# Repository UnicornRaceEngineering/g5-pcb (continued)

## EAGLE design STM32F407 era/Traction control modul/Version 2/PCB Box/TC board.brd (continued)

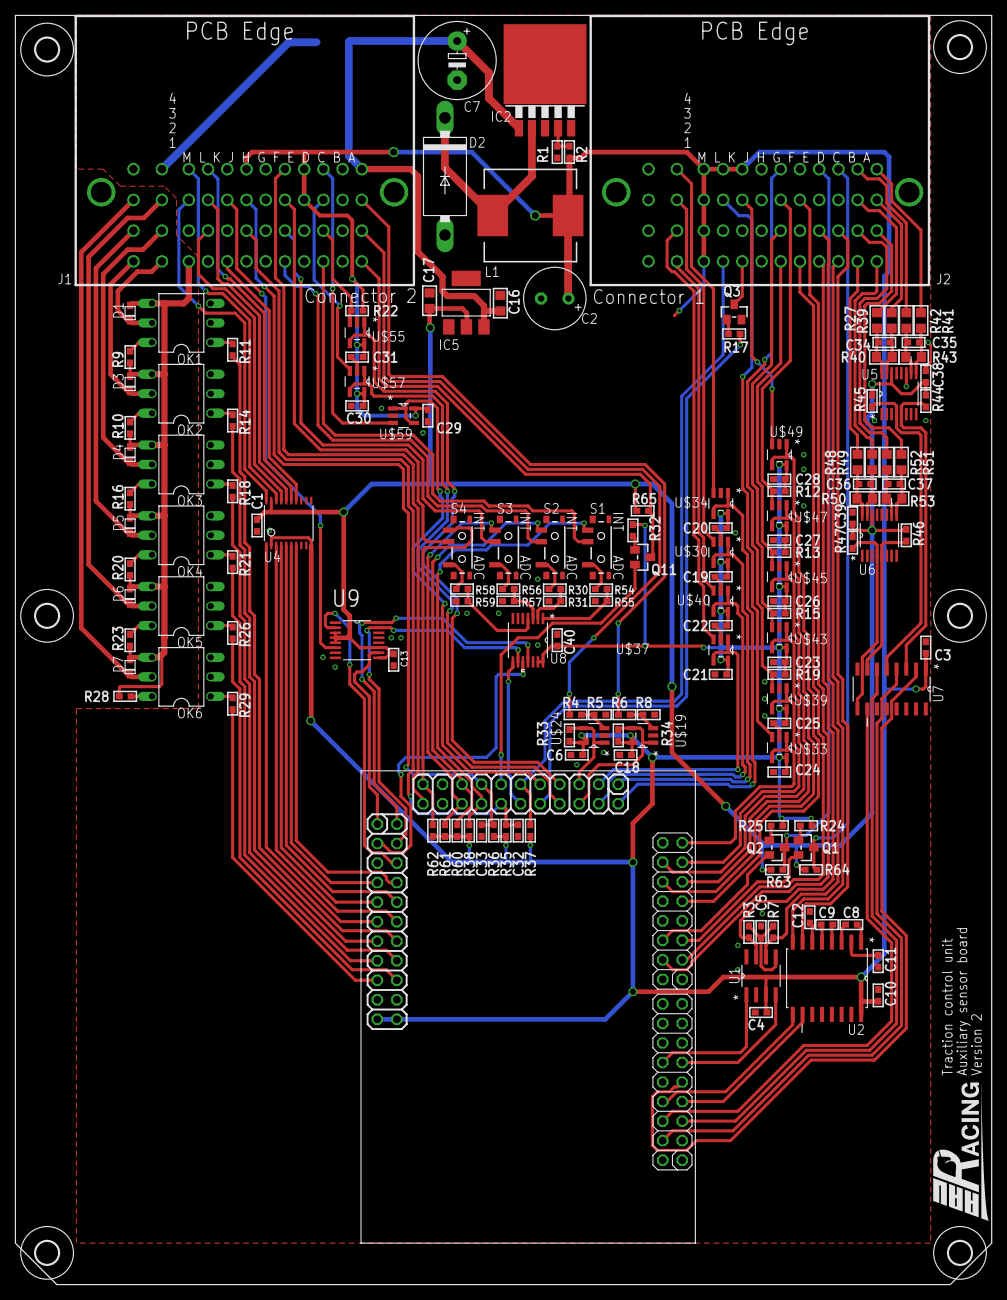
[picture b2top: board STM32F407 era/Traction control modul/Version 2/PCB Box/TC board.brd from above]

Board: 2 copper layers, 127.0 x 165.1 mm, 160 parts (1 on the bottom side), 156 nets.

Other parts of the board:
U9: AD5024BRUZ; SOP65P640X120-16N

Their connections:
5.0V: U9.3, U9.4, U9.5, U9.9, U9.11; also elsewhere on the board
DACCLR: U9.10; also elsewhere on the board
DACCS: U9.2; also elsewhere on the board
GND: U9.8, U9.14; also elsewhere on the board
MOSI: U9.15; also elsewhere on the board
SCK: U9.16; also elsewhere on the board
VOUT: U9.6; also elsewhere on the board

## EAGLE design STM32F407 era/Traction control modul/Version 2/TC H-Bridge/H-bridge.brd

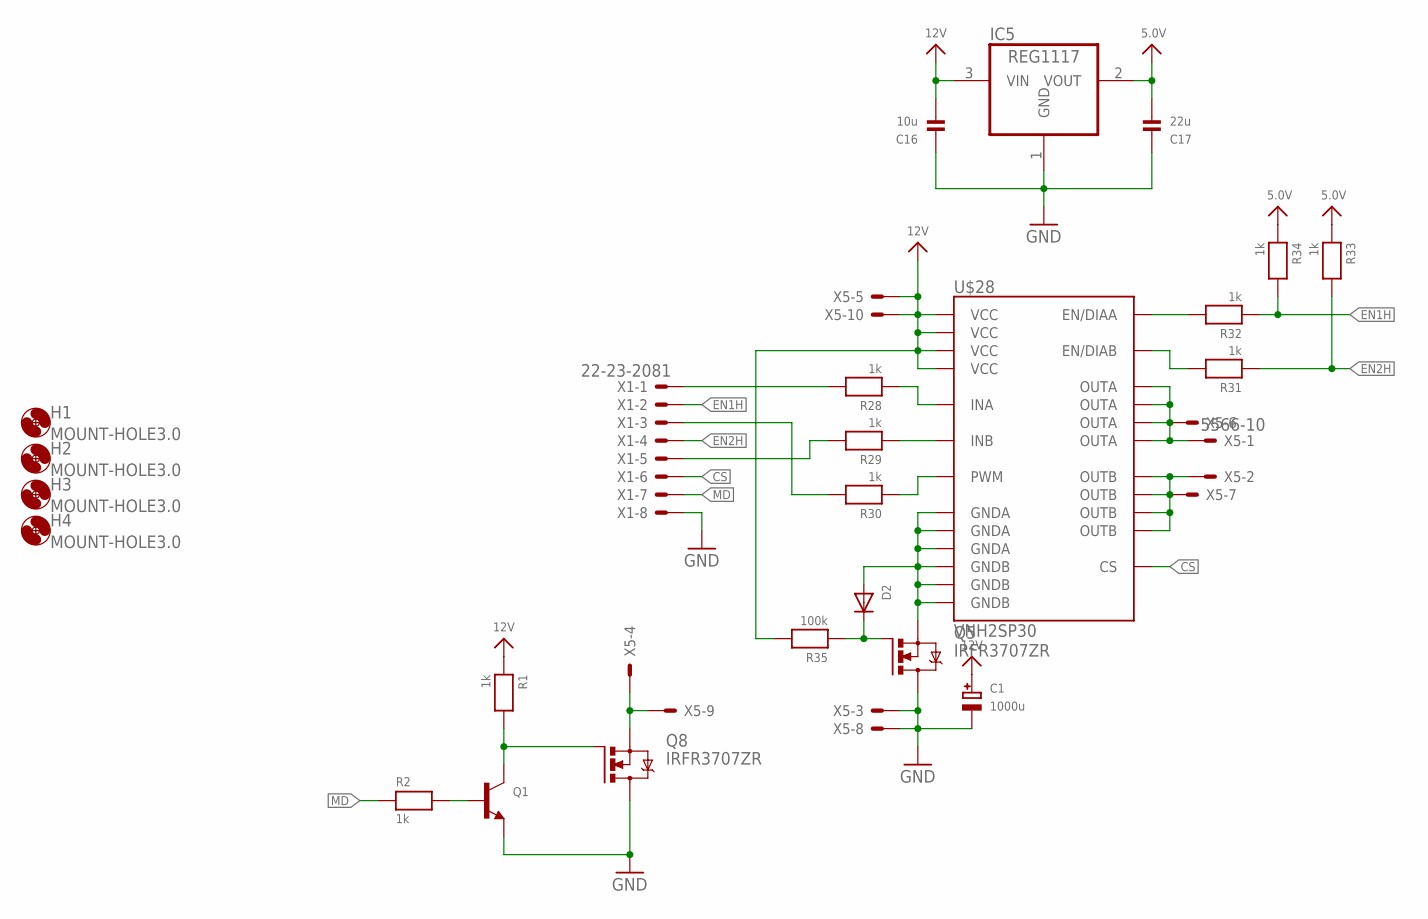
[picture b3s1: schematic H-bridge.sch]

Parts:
C1: 1000u; CELEC_3.5MM_10MM
C16: 10u; _0805
C17: 22u; _0805
D2: DIODESMA; SMADIODE
H1, H2, H3, H4: MOUNT-HOLE3.0; 3,0
IC5: REG1117; SOT223
Q1: TRANSISTOR_NPNWIDE; SOT23-WIDE
Q5, Q8: IRFR3707ZR; D-PAK_TO252AA
R1, R2, R28, R29, R30, R31, R32, R33, R34: 1k; _0603
R35: 100k; _0603
U$28: VNH2SP30
X1: 22-23-2081
X5: 5566-10

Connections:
5.0V: C17.2, IC5.2 (VOUT), R33.1, R34.1
12V: C1.+, C16.2, IC5.3 (VIN), R1.1, R35.2, U$28.3 (VCC), U$28.13 (VCC), U$28.23 (VCC), U$28.SLUG1 (VCC), X5.5, X5.10
CS: U$28.9 (CS), X1.6
CVVM: U$28.15 (OUTB), U$28.16 (OUTB), U$28.21 (OUTB), U$28.SLUG2 (OUTB), X5.2, X5.7
EN1H: R32.1, R34.2, X1.2
EN2H: R31.1, R33.2, X1.4
GND: C1.-, C16.1, C17.1, IC5.1 (GND), Q1.2 (E), Q5.4 (D), Q8.4 (D), X1.8, X5.3, X5.8
GNDM: Q8.3 (S), X5.4, X5.9
GNDS: D2.A, Q5.3 (S), U$28.18 (GNDB), U$28.19 (GNDB), U$28.20 (GNDB), U$28.26 (GNDA), U$28.27 (GNDA), U$28.28 (GNDA)
MD: R2.1, X1.7
unnamed: Q1.1 (B), R2.2
unnamed: Q1.3 (C), Q8.1 (G), R1.2
unnamed: R30.1, U$28.8 (PWM)
unnamed: R29.1, U$28.11 (INB)
unnamed: R28.1, U$28.5 (INA)
unnamed: R31.2, U$28.10 (EN/DIAB)
unnamed: R32.2, U$28.6 (EN/DIAA)
unnamed: D2.C, Q5.1 (G), R35.1
unnamed: R28.2, X1.1
unnamed: R29.2, X1.5
unnamed: R30.2, X1.3
OUTA: U$28.1 (OUTA), U$28.25 (OUTA), U$28.30 (OUTA), U$28.SLUG3 (OUTA), X5.1, X5.6

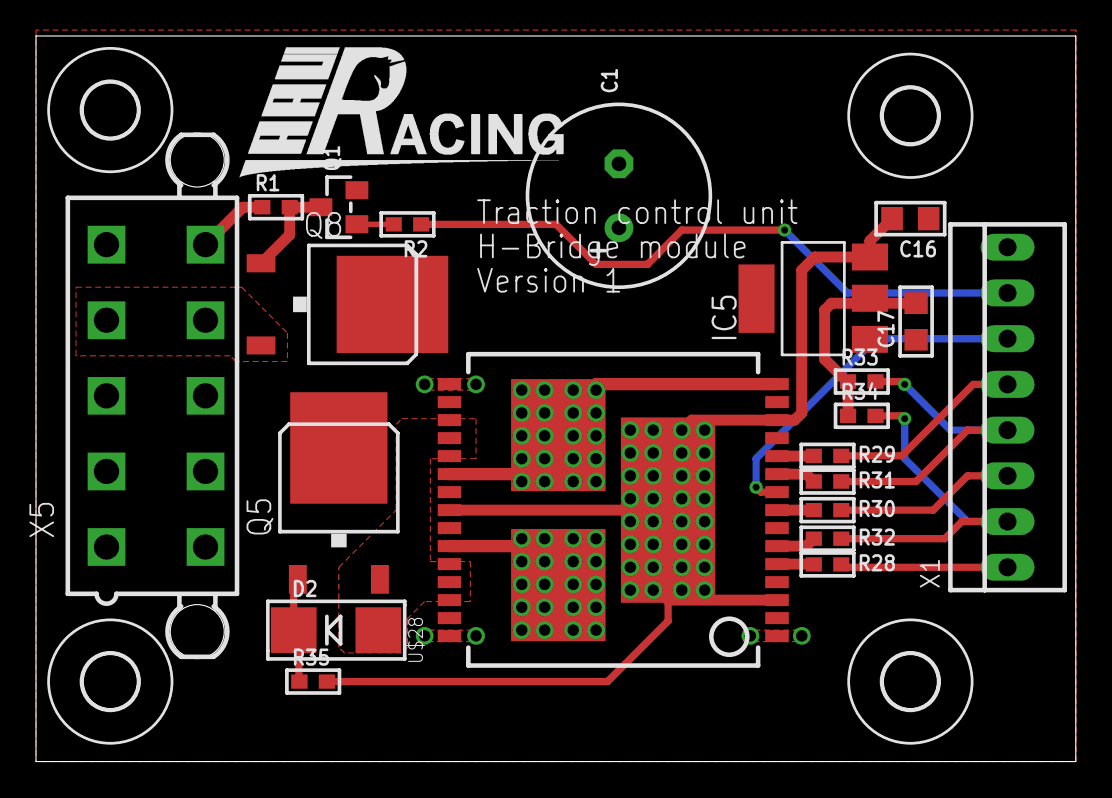
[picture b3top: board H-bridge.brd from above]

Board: 2 copper layers, 57.8 x 40.3 mm, 25 parts (0 on the bottom side), 22 nets.

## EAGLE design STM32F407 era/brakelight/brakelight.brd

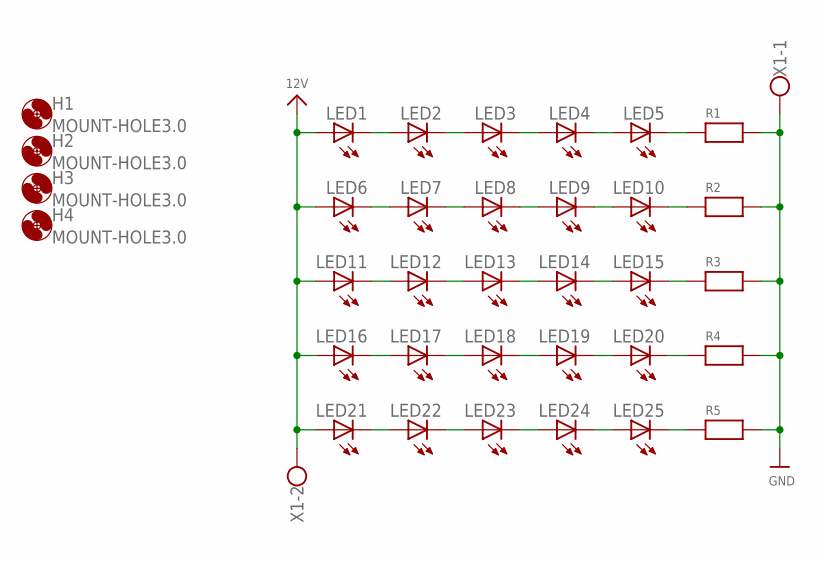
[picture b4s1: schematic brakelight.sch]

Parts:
H1, H2, H3, H4: MOUNT-HOLE3.0; 3,0
LED1, LED2, LED3, LED4, LED5, LED6, LED7, LED8, LED9, LED10, LED11, LED12, LED13, LED14, LED15, LED16, LED17, LED18, LED19, LED20, LED21, LED22, LED23, LED24, LED25: LEDP-LCC-2; P-LCC-2
R1, R2, R3, R4, R5: RESISTOR0805; 0805
X1: W237-102

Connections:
12V: LED1.A, LED6.A, LED11.A, LED16.A, LED21.A, X1.2
GND: R1.2, R2.2, R3.2, R4.2, R5.2, X1.1
unnamed: LED1.C, LED2.A
unnamed: LED6.C, LED7.A
unnamed: LED11.C, LED12.A
unnamed: LED16.C, LED17.A
unnamed: LED21.C, LED22.A
unnamed: LED2.C, LED3.A
unnamed: LED7.C, LED8.A
unnamed: LED12.C, LED13.A
unnamed: LED17.C, LED18.A
unnamed: LED22.C, LED23.A
unnamed: LED3.C, LED4.A
unnamed: LED8.C, LED9.A
unnamed: LED13.C, LED14.A
unnamed: LED18.C, LED19.A
unnamed: LED23.C, LED24.A
unnamed: LED4.C, LED5.A
unnamed: LED9.C, LED10.A
unnamed: LED14.C, LED15.A
unnamed: LED19.C, LED20.A
unnamed: LED24.C, LED25.A
unnamed: LED5.C, R1.1
unnamed: LED10.C, R2.1
unnamed: LED15.C, R3.1
unnamed: LED20.C, R4.1
unnamed: LED25.C, R5.1

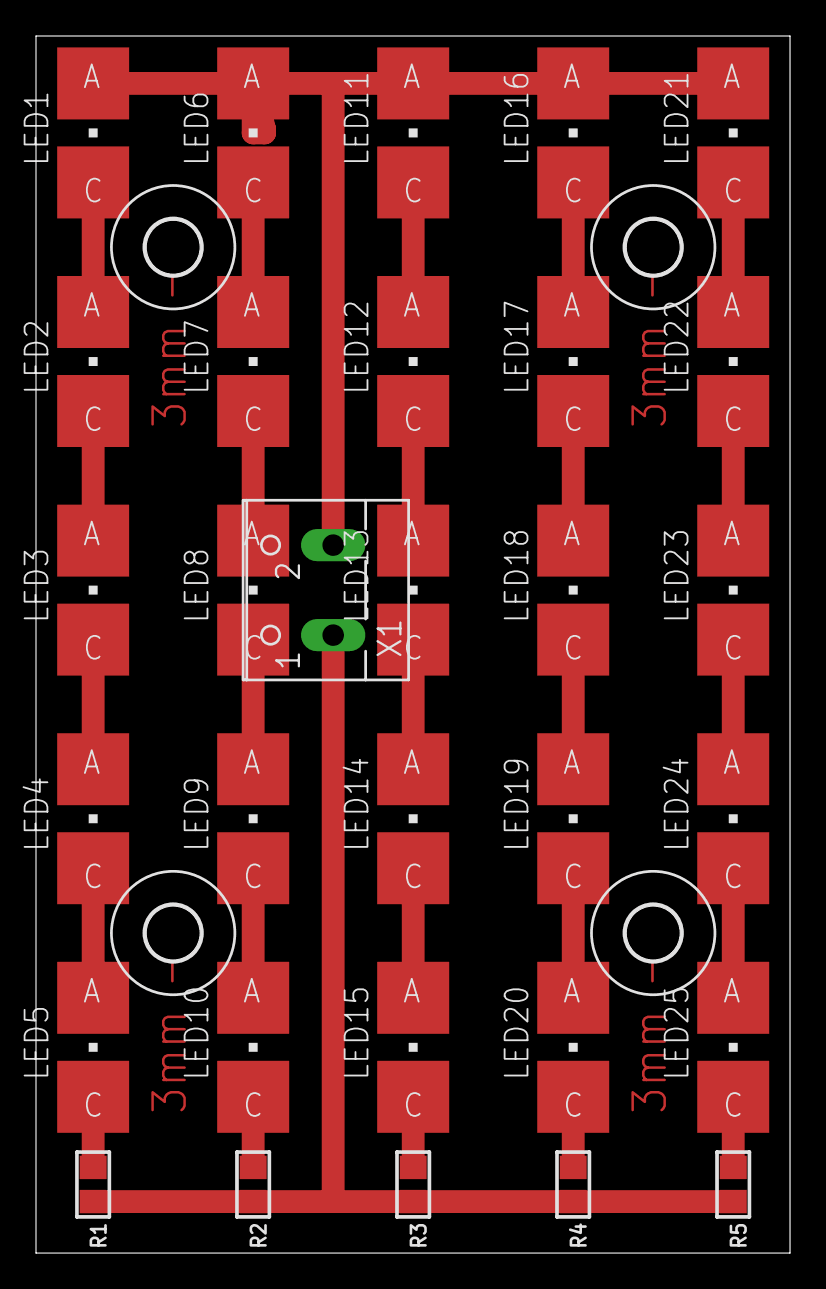
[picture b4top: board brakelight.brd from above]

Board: 2 copper layers, 41.9 x 67.6 mm, 35 parts (0 on the bottom side), 27 nets.

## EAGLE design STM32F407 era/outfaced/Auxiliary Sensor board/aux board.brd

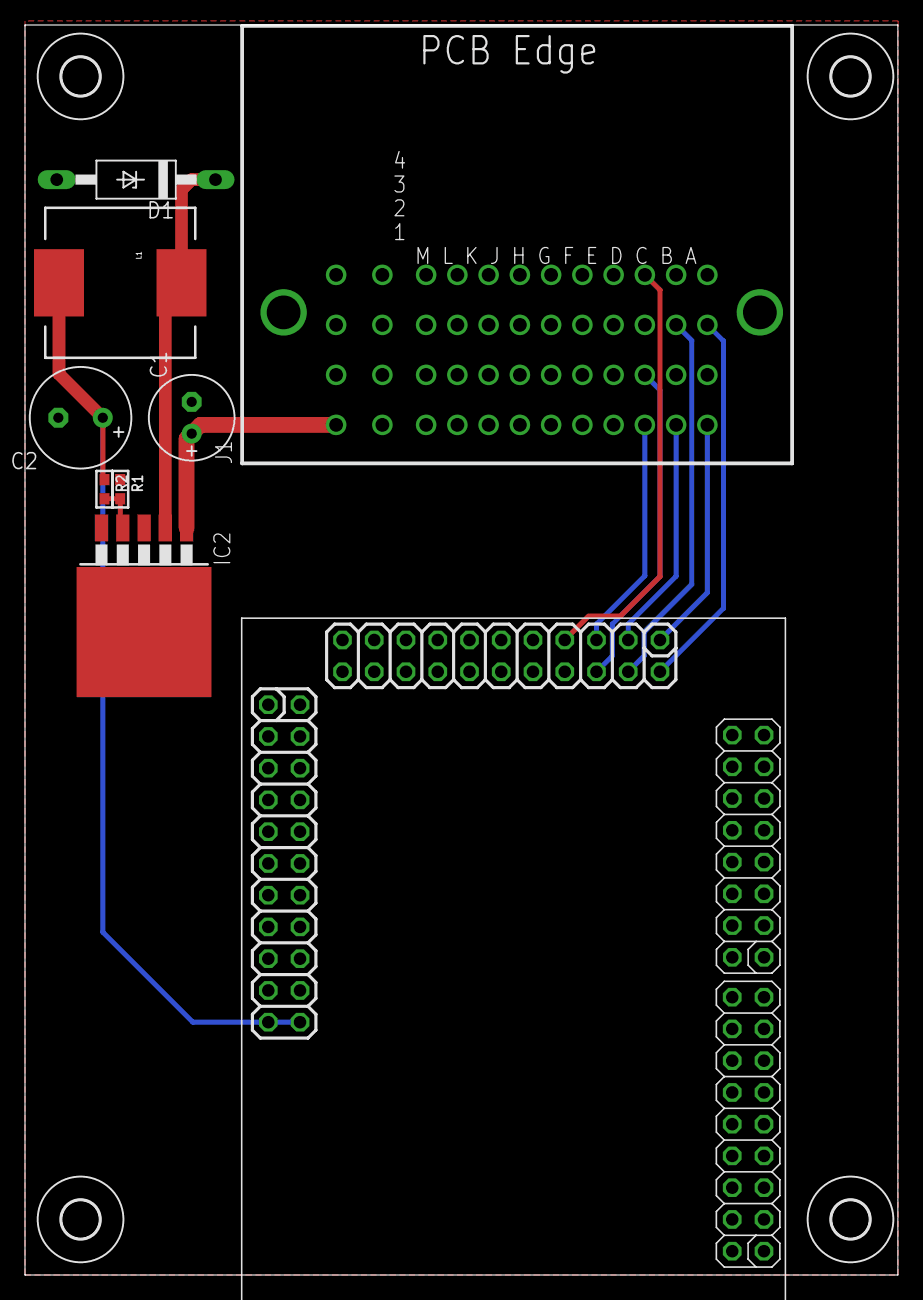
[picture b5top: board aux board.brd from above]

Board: 2 copper layers, 69.8 x 100.0 mm, 13 parts (0 on the bottom side), 12 nets.

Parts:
C1: 100u; E2,5-7
C2: 220uf; E3,5-8
D1: 1n5824; F126Z12
H1, H2, H3, H4: MOUNT-HOLE3.0; 3,0
IC2: lm2575; TO263-5
J1: AUTOCONNECTOR
L1: MSS1278-224KLD; CDRH125
R1: 1k; _0603
R2: 1k69; _0603
U$1: CPU-BOARD; CPU-BOARD-JP1

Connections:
3.3V: C2.+, L1.2, R2.1, U$1.P$43, U$1.P$44
12V: C1.+, IC2.1, J1.M1
BRAKEP1: J1.B1, U$1.P$3
BRAKEP2: J1.B3, U$1.P$4
GND: C1.-, C2.-, D1.A, IC2.3, IC2.5, IC2.6, J1.A2, J1.A4, J1.B2, J1.B4, J1.C3, J1.L1, R1.1, U$1.P$21, U$1.P$22, U$1.P$41, U$1.P$42, U$1.P$62, U$1.P$69, U$1.P$70, U$1.P$78
IGNCUT: J1.C2, U$1.P$6
unnamed: IC2.4, R1.2, R2.2
unnamed: D1.C, IC2.2, L1.1
NEUTRAL: J1.C1, U$1.P$5
OILP: J1.C4, U$1.P$7
VANDT1: J1.A1, U$1.P$1
VANDT2: J1.A3, U$1.P$2

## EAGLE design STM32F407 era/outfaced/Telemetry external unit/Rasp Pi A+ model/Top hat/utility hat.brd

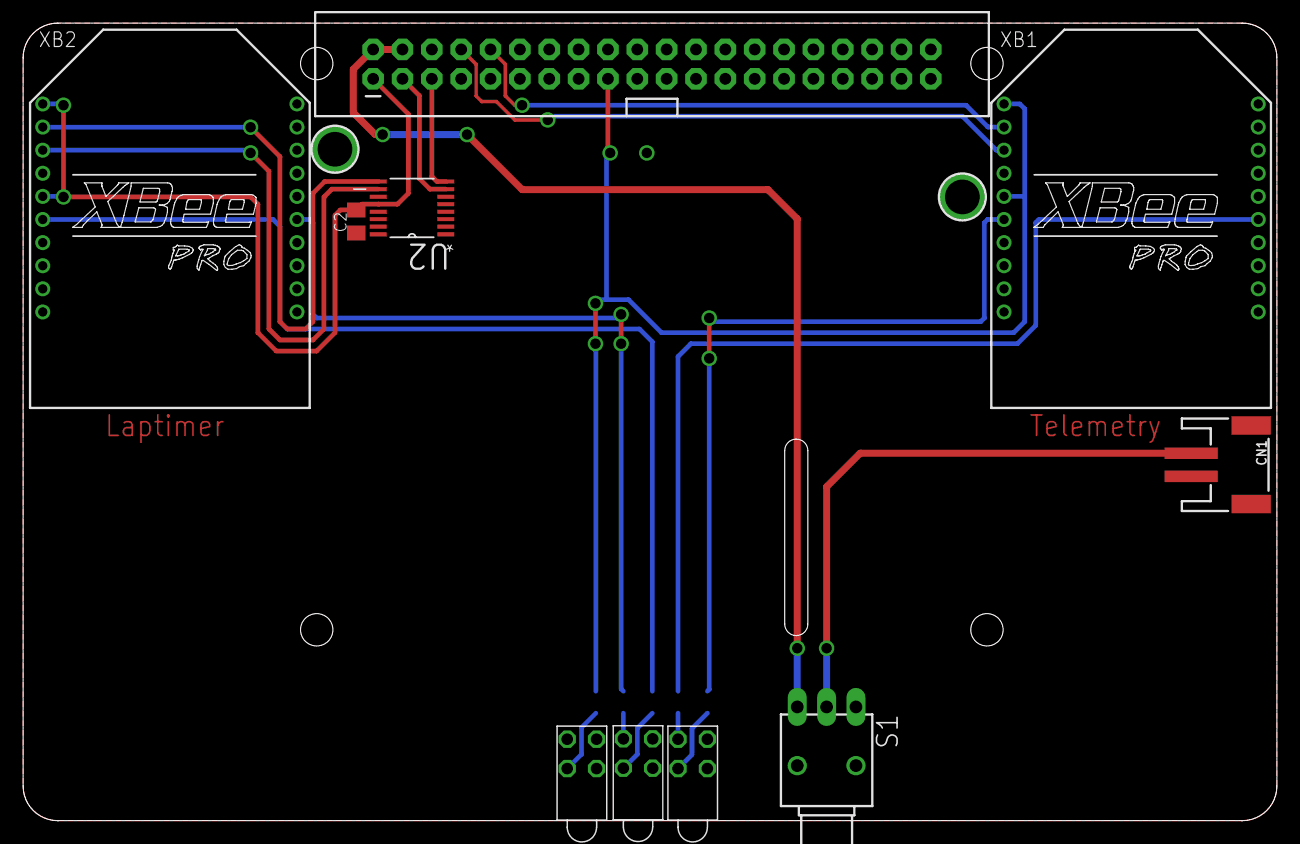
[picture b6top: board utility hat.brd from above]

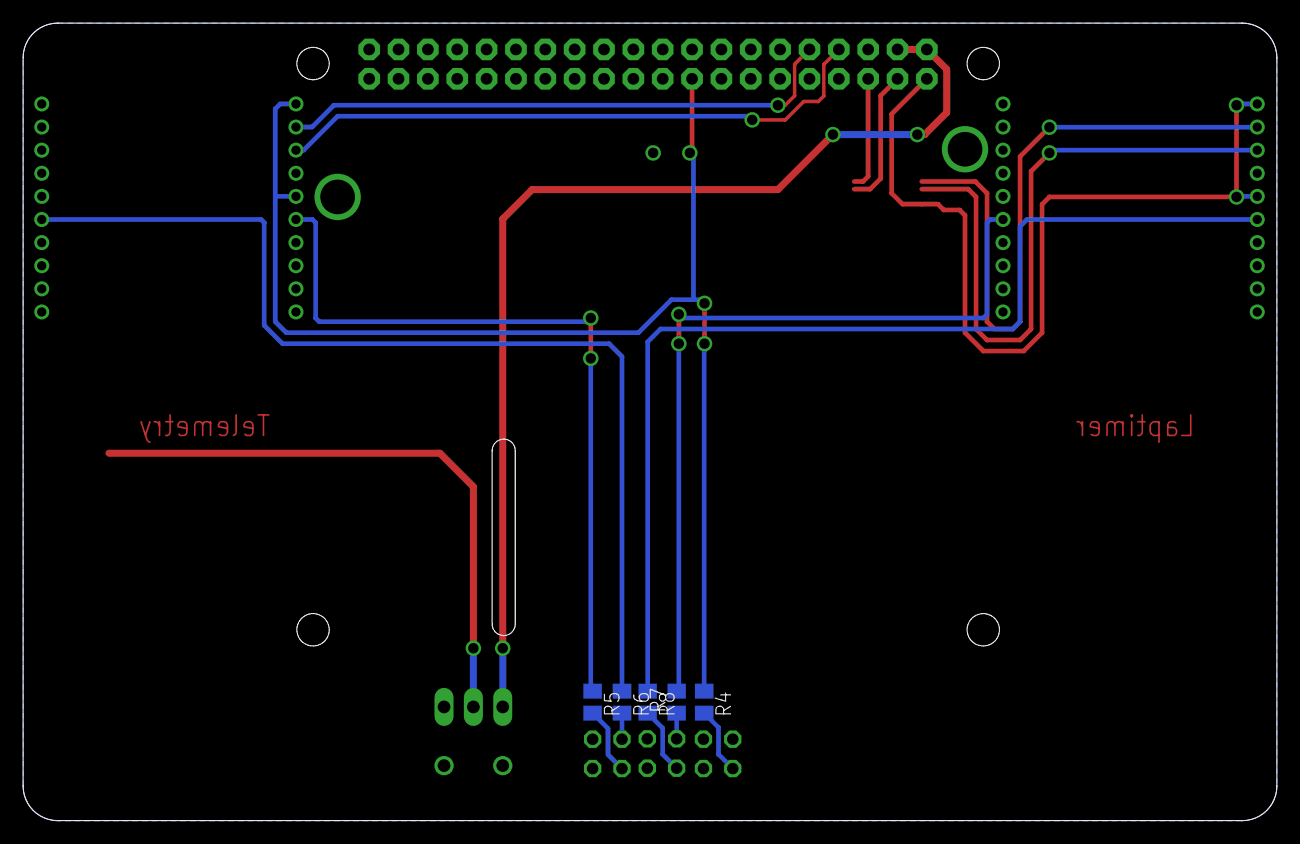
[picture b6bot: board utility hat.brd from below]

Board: 2 copper layers, 108.5 x 69.0 mm, 17 parts (5 on the bottom side), 19 nets.

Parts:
C2: 100nF; C0805K
CN1: JSTPH2
JP1: RASPBERRYPI-B+-GPIO; 2X20-SHROUDED
R4: 1k; M0805
R5, R6, R7, R8: 3k9; M0805
S1: TL36WO; TL3XWO
U2: SC18IM700IPW,112; SOP65P640X110-16N
U$1, U$2, U$3: BI-LEVEL-LED-INDICATOR
U$4, U$5: MOUNTINGHOLE3.0THIN; MOUNTINGHOLE_3.0_PLATEDTHIN
XB1, XB2: XBEE-PRO

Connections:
+3V3: C2.2, JP1.1, JP1.17, R4.1, U2.12, XB1.1, XB1.5, XB2.1, XB2.5
+5V: JP1.2, JP1.4, S1.3
GND: C2.1, CN1.2, JP1.6, JP1.9, JP1.14, JP1.20, JP1.25, JP1.30, JP1.34, JP1.39, U2.4, U$1.CATHODE1, U$1.CATHODE2, U$2.CATHODE1, U$2.CATHODE2, U$3.CATHODE1, U$3.CATHODE2, XB1.10, XB2.10
unnamed: U2.10, XB2.3
unnamed: U2.9, XB2.2
unnamed: R4.2, U$3.ANODE1
unnamed: R6.1, XB1.15
unnamed: R6.2, U$1.ANODE2
unnamed: R5.1, XB1.6
unnamed: R5.2, U$1.ANODE1
unnamed: R7.1, U$2.ANODE2
unnamed: R8.2, U$2.ANODE1
unnamed: R7.2, XB2.15
unnamed: R8.1, XB2.6
unnamed: CN1.1, S1.2
RX: JP1.10, XB1.2
SCL: JP1.5, U2.8
SDA: JP1.3, U2.7
TX: JP1.8, XB1.3
